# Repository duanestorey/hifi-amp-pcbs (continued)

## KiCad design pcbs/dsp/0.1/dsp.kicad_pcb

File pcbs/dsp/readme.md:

## Digital Signal Processing (DSP)

This PCB allows switching of 4 analog stereo inputs and one 5.1 channel input into 5.1.  Channels that are missing
can be created.  It is based on the AX2358 IC.

### Version History

- 1.0: Initial Release
- 1.2: Did an initial build.  Seems like there is digital noise on the output, likely from the I2C signals sharing the audio ground.  This design now has a digital and analog ground on the board - it'll use the digital ground for the AX2358 IC, but use the analog ground for the channel outputs.

### Speciality Components

* AX2358 Channel switching IC
* Nichicon Muse ES 25V 10uF

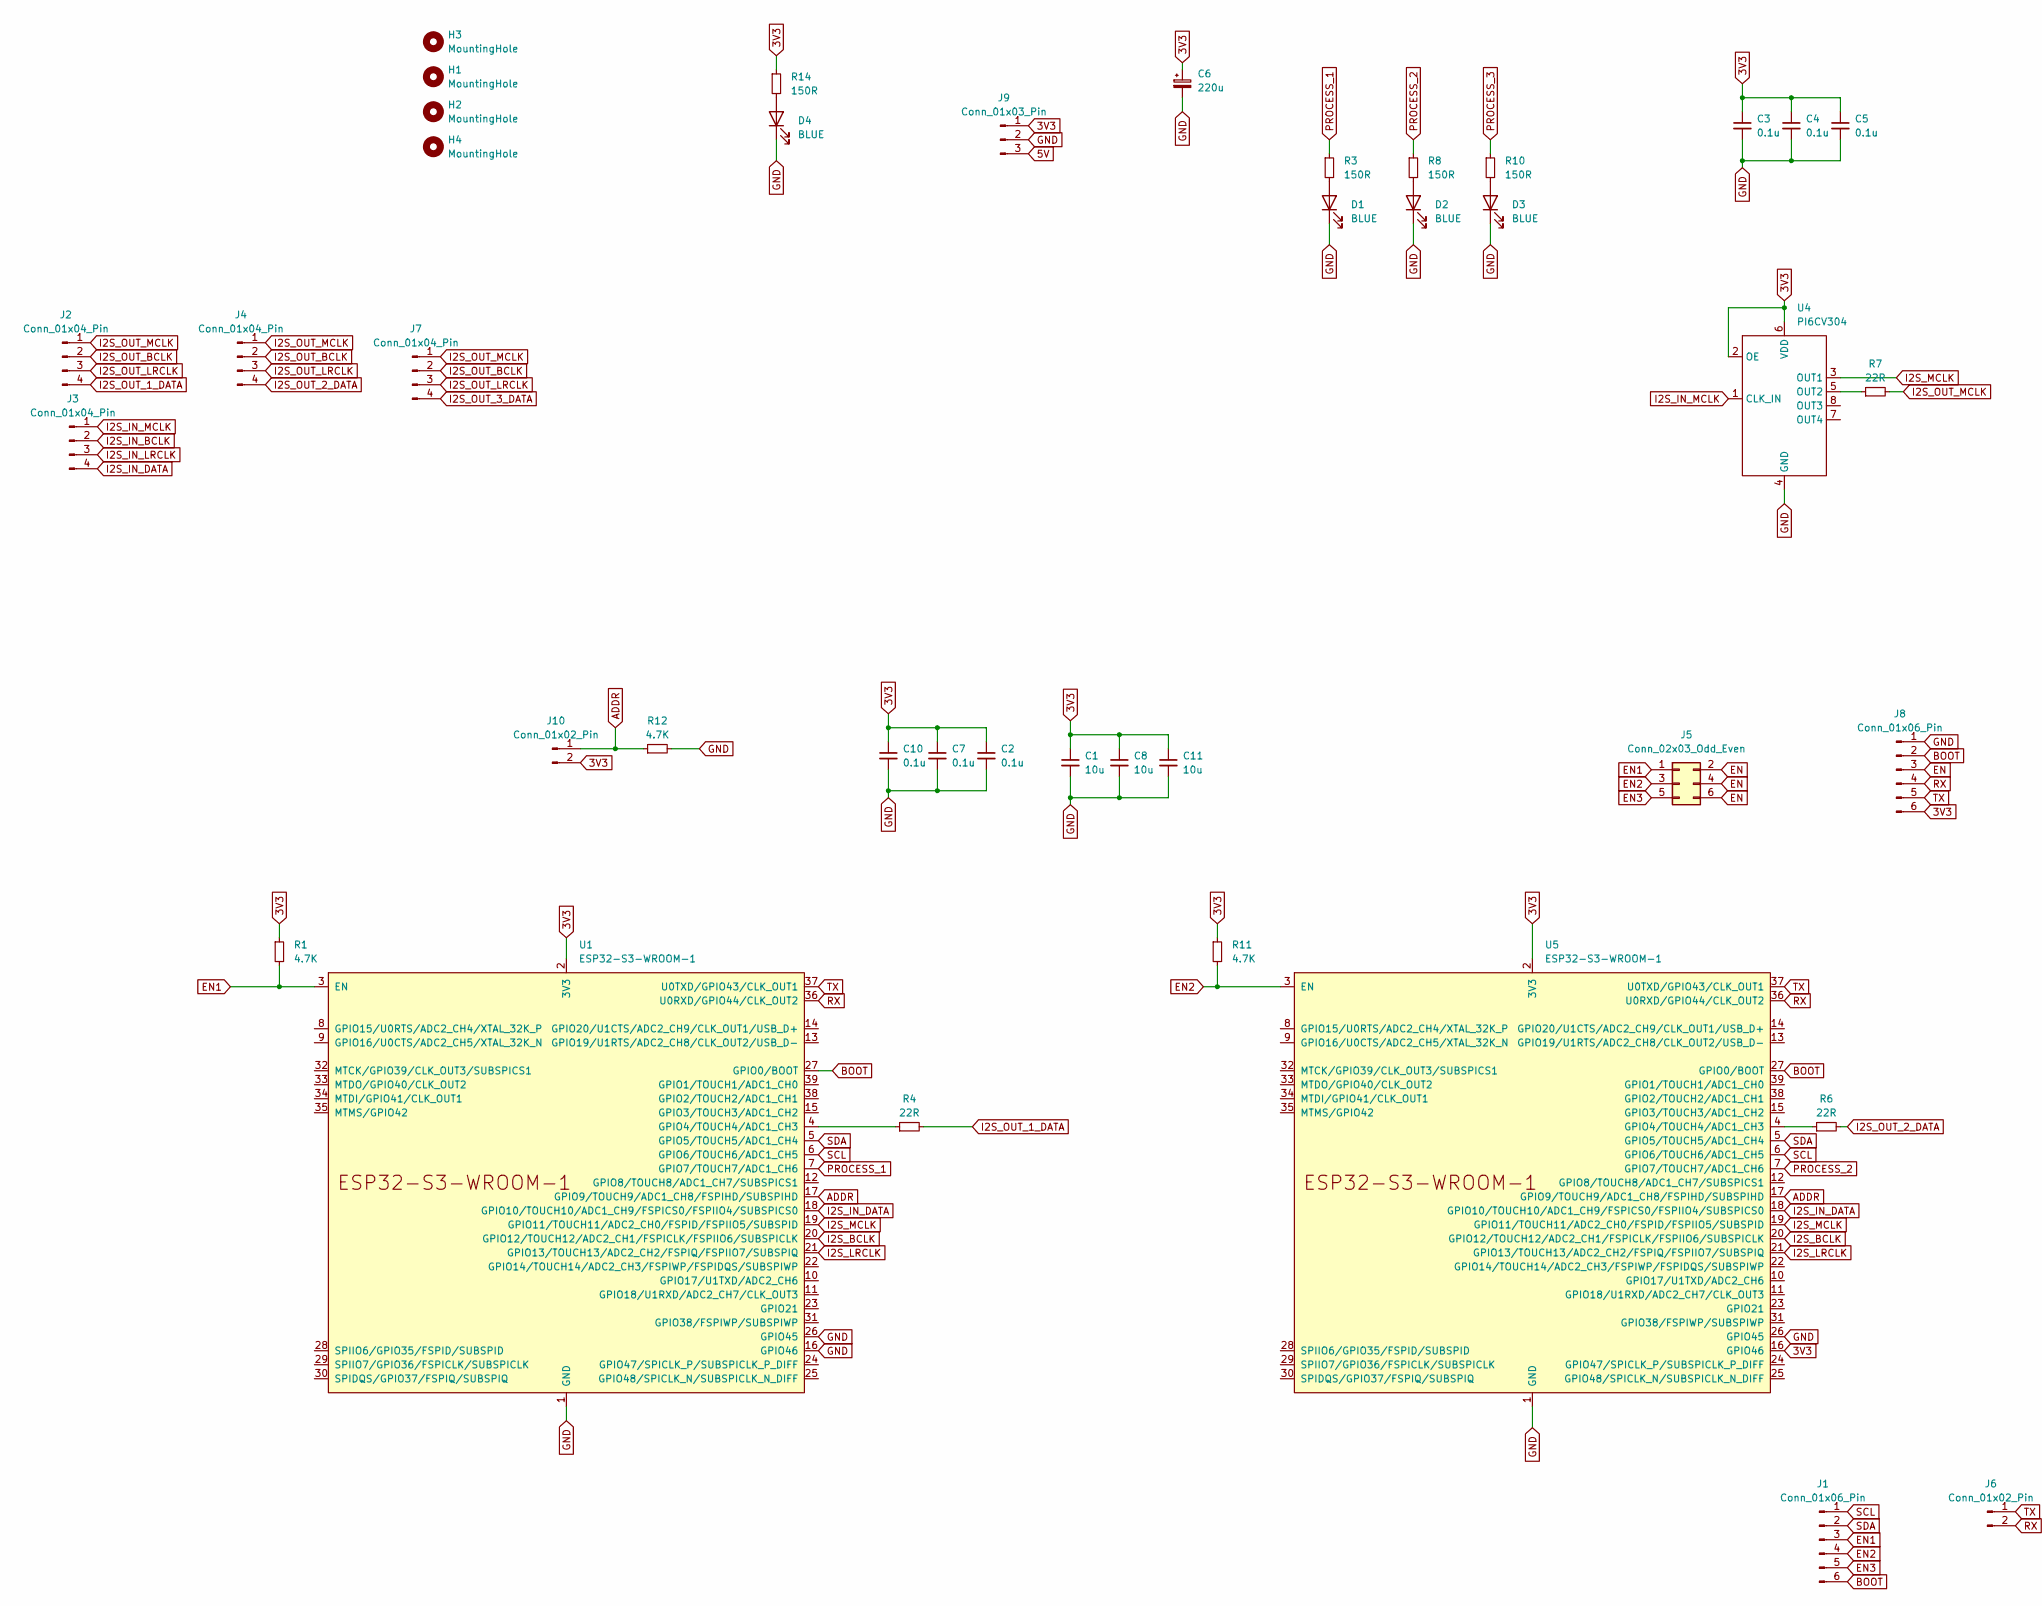
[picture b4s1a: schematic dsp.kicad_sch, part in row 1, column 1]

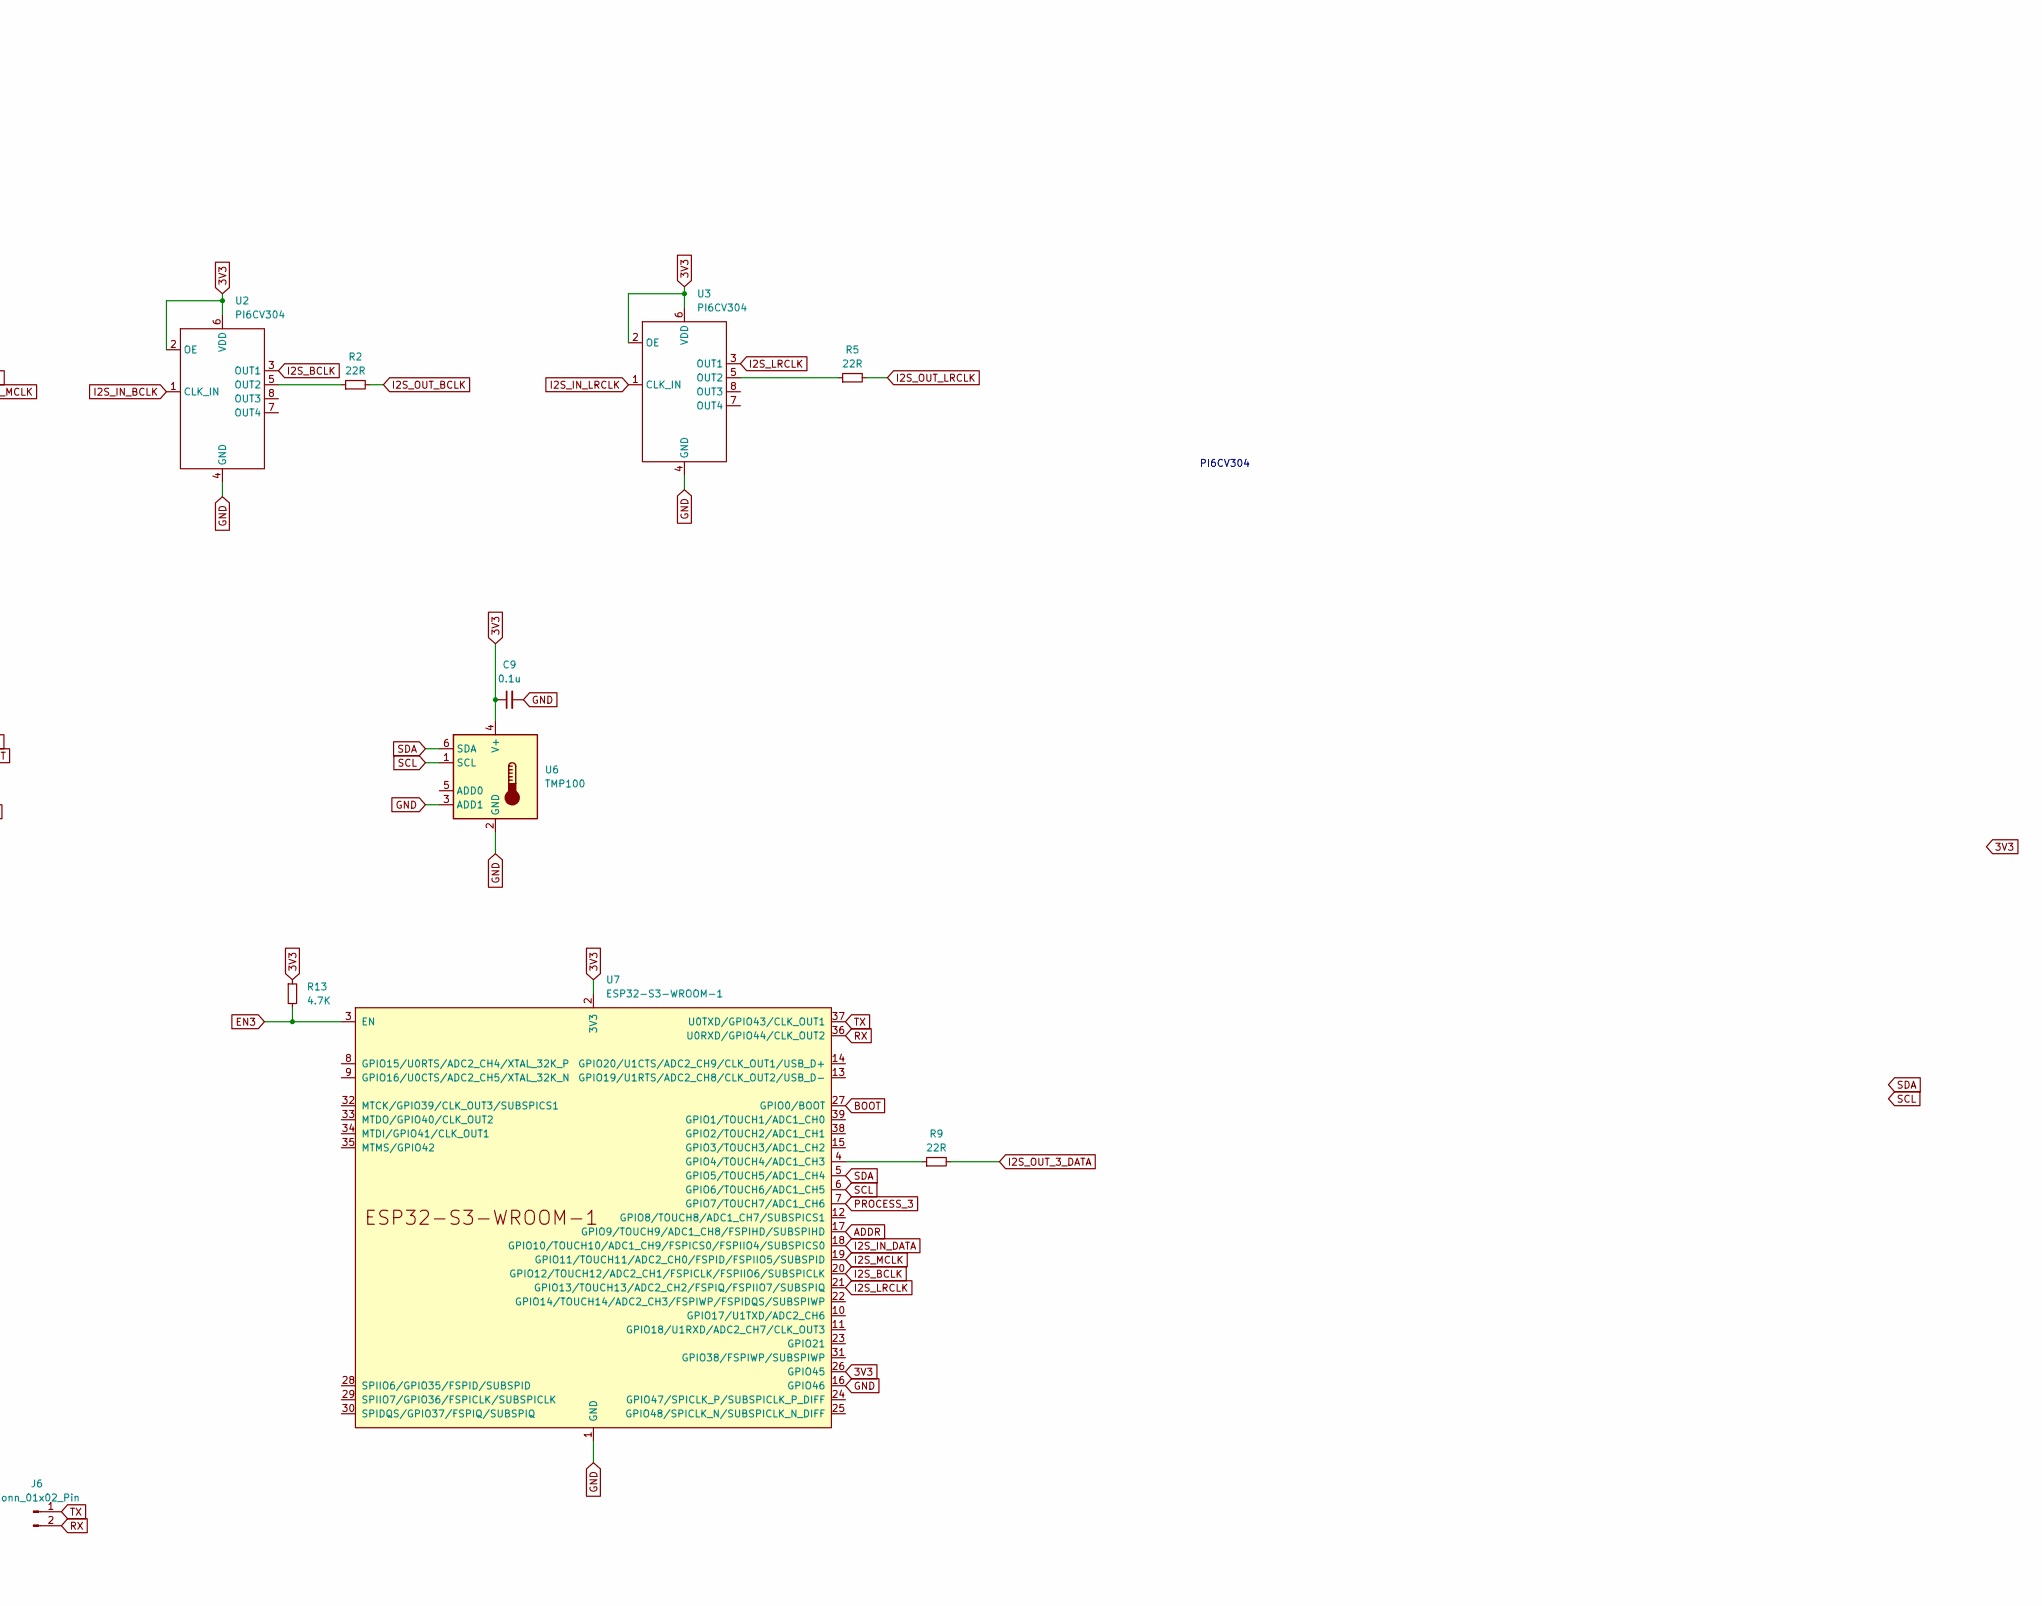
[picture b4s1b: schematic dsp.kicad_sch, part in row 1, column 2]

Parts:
C1, C8, C11: 10u; C_0805_2012Metric_Pad1.18x1.45mm_HandSolder
C2, C3, C4, C5, C7, C9, C10: 0.1u; C_0603_1608Metric_Pad1.08x0.95mm_HandSolder
C6: 220u; CP_Radial_D6.3mm_P2.50mm; LCSC C4747974
D1, D2, D3, D4: BLUE; D_0603_1608Metric; LCSC C84259
H1, H2, H3, H4: MountingHole; MountingHole_3.2mm_M3_DIN965_Pad_TopOnly
J1: Conn_01x06_Pin; JST_PH_B6B-PH-K_1x06_P2.00mm_Vertical
J2, J3, J4, J7: Conn_01x04_Pin; JST_PH_B4B-PH-K_1x04_P2.00mm_Vertical
J5: Conn_02x03_Odd_Even; PinHeader_2x03_P2.54mm_Vertical
J6: Conn_01x02_Pin; JST_PH_B2B-PH-K_1x02_P2.00mm_Vertical
J8: Conn_01x06_Pin; PinHeader_1x06_P2.54mm_Vertical
J9: Conn_01x03_Pin; JST_PH_B3B-PH-K_1x03_P2.00mm_Vertical
J10: Conn_01x02_Pin; PinHeader_1x02_P2.54mm_Vertical
R1, R11, R12, R13: 4.7K; R_0603_1608Metric; LCSC C23162
R2, R4, R5, R6, R7, R9: 22R; R_0603_1608Metric
R3, R8, R10, R14: 150R; R_0603_1608Metric; LCSC C22808
U1, U5, U7: ESP32-S3-WROOM-1; Mouser 356-ESP32S3WRM1N16R8
U2, U3, U4: PI6CV304; TSSOP-8_4.4x3mm_P0.65mm
U6: TMP100; SOT-23-6

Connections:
3V3: C1.1, C2.1, C3.1, C4.1, C5.1, C6.1, C7.1, C8.1, C9.1, C10.1, C11.1, J8.6, J9.1, J10.2, R1.1, R11.1, R13.1, R14.1, U1.2 (3V3), U2.2 (OE), U2.6 (VDD), U3.2 (OE), U3.6 (VDD), U4.2 (OE), U4.6 (VDD), U5.2 (3V3), U5.16 (GPIO46), U6.4 (V+), U7.2 (3V3), U7.26 (GPIO45)
5V: J9.3
ADDR: J10.1, R12.1, U1.17 (GPIO9/TOUCH9/ADC1_CH8/FSPIHD/SUBSPIHD), U5.17 (GPIO9/TOUCH9/ADC1_CH8/FSPIHD/SUBSPIHD), U7.17 (GPIO9/TOUCH9/ADC1_CH8/FSPIHD/SUBSPIHD)
BOOT: J1.6, J8.2, U1.27 (GPIO0/BOOT), U5.27 (GPIO0/BOOT), U7.27 (GPIO0/BOOT)
EN: J5.2, J5.4, J5.6, J8.3
EN1: J1.3, J5.1, R1.2, U1.3 (EN)
EN2: J1.4, J5.3, R11.2, U5.3 (EN)
EN3: J1.5, J5.5, R13.2, U7.3 (EN)
GND: C1.2, C2.2, C3.2, C4.2, C5.2, C6.2, C7.2, C8.2, C9.2, C10.2, C11.2, D1.1 (K), D2.1 (K), D3.1 (K), D4.1 (K), J8.1, J9.2, R12.2, U1.1 (GND), U1.16 (GPIO46), U1.26 (GPIO45), U1.40 (GND), U1.41 (GND), U2.4 (GND), U3.4 (GND), U4.4 (GND), U5.1 (GND), U5.26 (GPIO45), U5.40 (GND), U5.41 (GND), U6.2 (GND), U6.3 (ADD1), U7.1 (GND), U7.16 (GPIO46), U7.40 (GND), U7.41 (GND)
I2S_BCLK: U1.20 (GPIO12/TOUCH12/ADC2_CH1/FSPICLK/FSPIIO6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), U2.3 (OUT1), U5.20 (GPIO12/TOUCH12/ADC2_CH1/FSPICLK/FSPIIO6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), U7.20 (GPIO12/TOUCH12/ADC2_CH1/FSPICLK/FSPIIO6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)
I2S_IN_BCLK: J3.2, U2.1 (CLK_IN)
I2S_IN_DATA: J3.4, U1.18 (GPIO10/TOUCH10/ADC1_CH9/FSPICS0/FSPIIO4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), U5.18 (GPIO10/TOUCH10/ADC1_CH9/FSPICS0/FSPIIO4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), U7.18 (GPIO10/TOUCH10/ADC1_CH9/FSPICS0/FSPIIO4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)
I2S_IN_LRCLK: J3.3, U3.1 (CLK_IN)
I2S_IN_MCLK: J3.1, U4.1 (CLK_IN)
I2S_LRCLK: U1.21 (GPIO13/TOUCH13/ADC2_CH2/FSPIQ/FSPIIO7/S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), U3.3 (OUT1), U5.21 (GPIO13/TOUCH13/ADC2_CH2/FSPIQ/FSPIIO7/S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), U7.21 (GPIO13/TOUCH13/ADC2_CH2/FSPIQ/FSPIIO7/S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)
I2S_MCLK: U1.19 (GPIO11/TOUCH11/ADC2_CH0/FSPID/FSPIIO5/S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), U4.3 (OUT1), U5.19 (GPIO11/TOUCH11/ADC2_CH0/FSPID/FSPIIO5/S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), U7.19 (GPIO11/TOUCH11/ADC2_CH0/FSPID/FSPIIO5/S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)
I2S_OUT_1_DATA: J2.4, R4.2
I2S_OUT_2_DATA: J4.4, R6.2
I2S_OUT_3_DATA: J7.4, R9.2
I2S_OUT_BCLK: J2.2, J4.2, J7.2, R2.2
I2S_OUT_LRCLK: J2.3, J4.3, J7.3, R5.2
I2S_OUT_MCLK: J2.1, J4.1, J7.1, R7.2
unnamed: D1.2 (A), R3.2
unnamed: D2.2 (A), R8.2
unnamed: D3.2 (A), R10.2
unnamed: D4.2 (A), R14.2
unnamed: R4.1, U1.4 (GPIO4/TOUCH4/ADC1_CH3)
unnamed: R2.1, U2.5 (OUT2)
unnamed: R5.1, U3.5 (OUT2)
unnamed: R7.1, U4.5 (OUT2)
unnamed: R6.1, U5.4 (GPIO4/TOUCH4/ADC1_CH3)
unnamed: R9.1, U7.4 (GPIO4/TOUCH4/ADC1_CH3)
PROCESS_1: R3.1, U1.7 (GPIO7/TOUCH7/ADC1_CH6)
PROCESS_2: R8.1, U5.7 (GPIO7/TOUCH7/ADC1_CH6)
PROCESS_3: R10.1, U7.7 (GPIO7/TOUCH7/ADC1_CH6)
RX: J6.2, J8.4, U1.36 (U0RXD/GPIO44/CLK_OUT2), U5.36 (U0RXD/GPIO44/CLK_OUT2), U7.36 (U0RXD/GPIO44/CLK_OUT2)
SCL: J1.1, U1.6 (GPIO6/TOUCH6/ADC1_CH5), U5.6 (GPIO6/TOUCH6/ADC1_CH5), U6.1 (SCL), U7.6 (GPIO6/TOUCH6/ADC1_CH5)
SDA: J1.2, U1.5 (GPIO5/TOUCH5/ADC1_CH4), U5.5 (GPIO5/TOUCH5/ADC1_CH4), U6.6 (SDA), U7.5 (GPIO5/TOUCH5/ADC1_CH4)
TX: J6.1, J8.5, U1.37 (U0TXD/GPIO43/CLK_OUT1), U5.37 (U0TXD/GPIO43/CLK_OUT1), U7.37 (U0TXD/GPIO43/CLK_OUT1)

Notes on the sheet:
PI6CV304

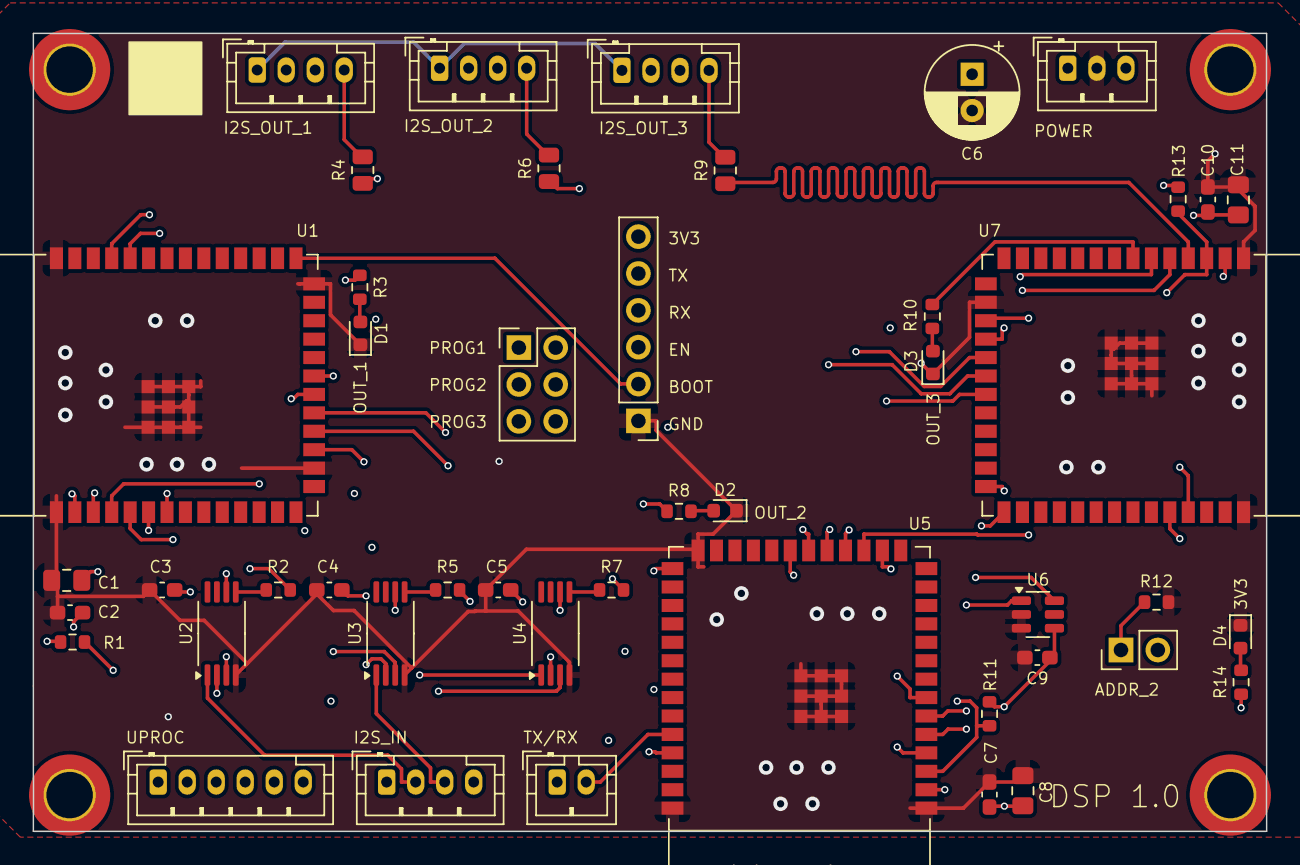
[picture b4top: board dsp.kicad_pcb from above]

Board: 4 copper layers, 85.0 x 55.0 mm, 50 parts (0 on the bottom side), 38 nets.

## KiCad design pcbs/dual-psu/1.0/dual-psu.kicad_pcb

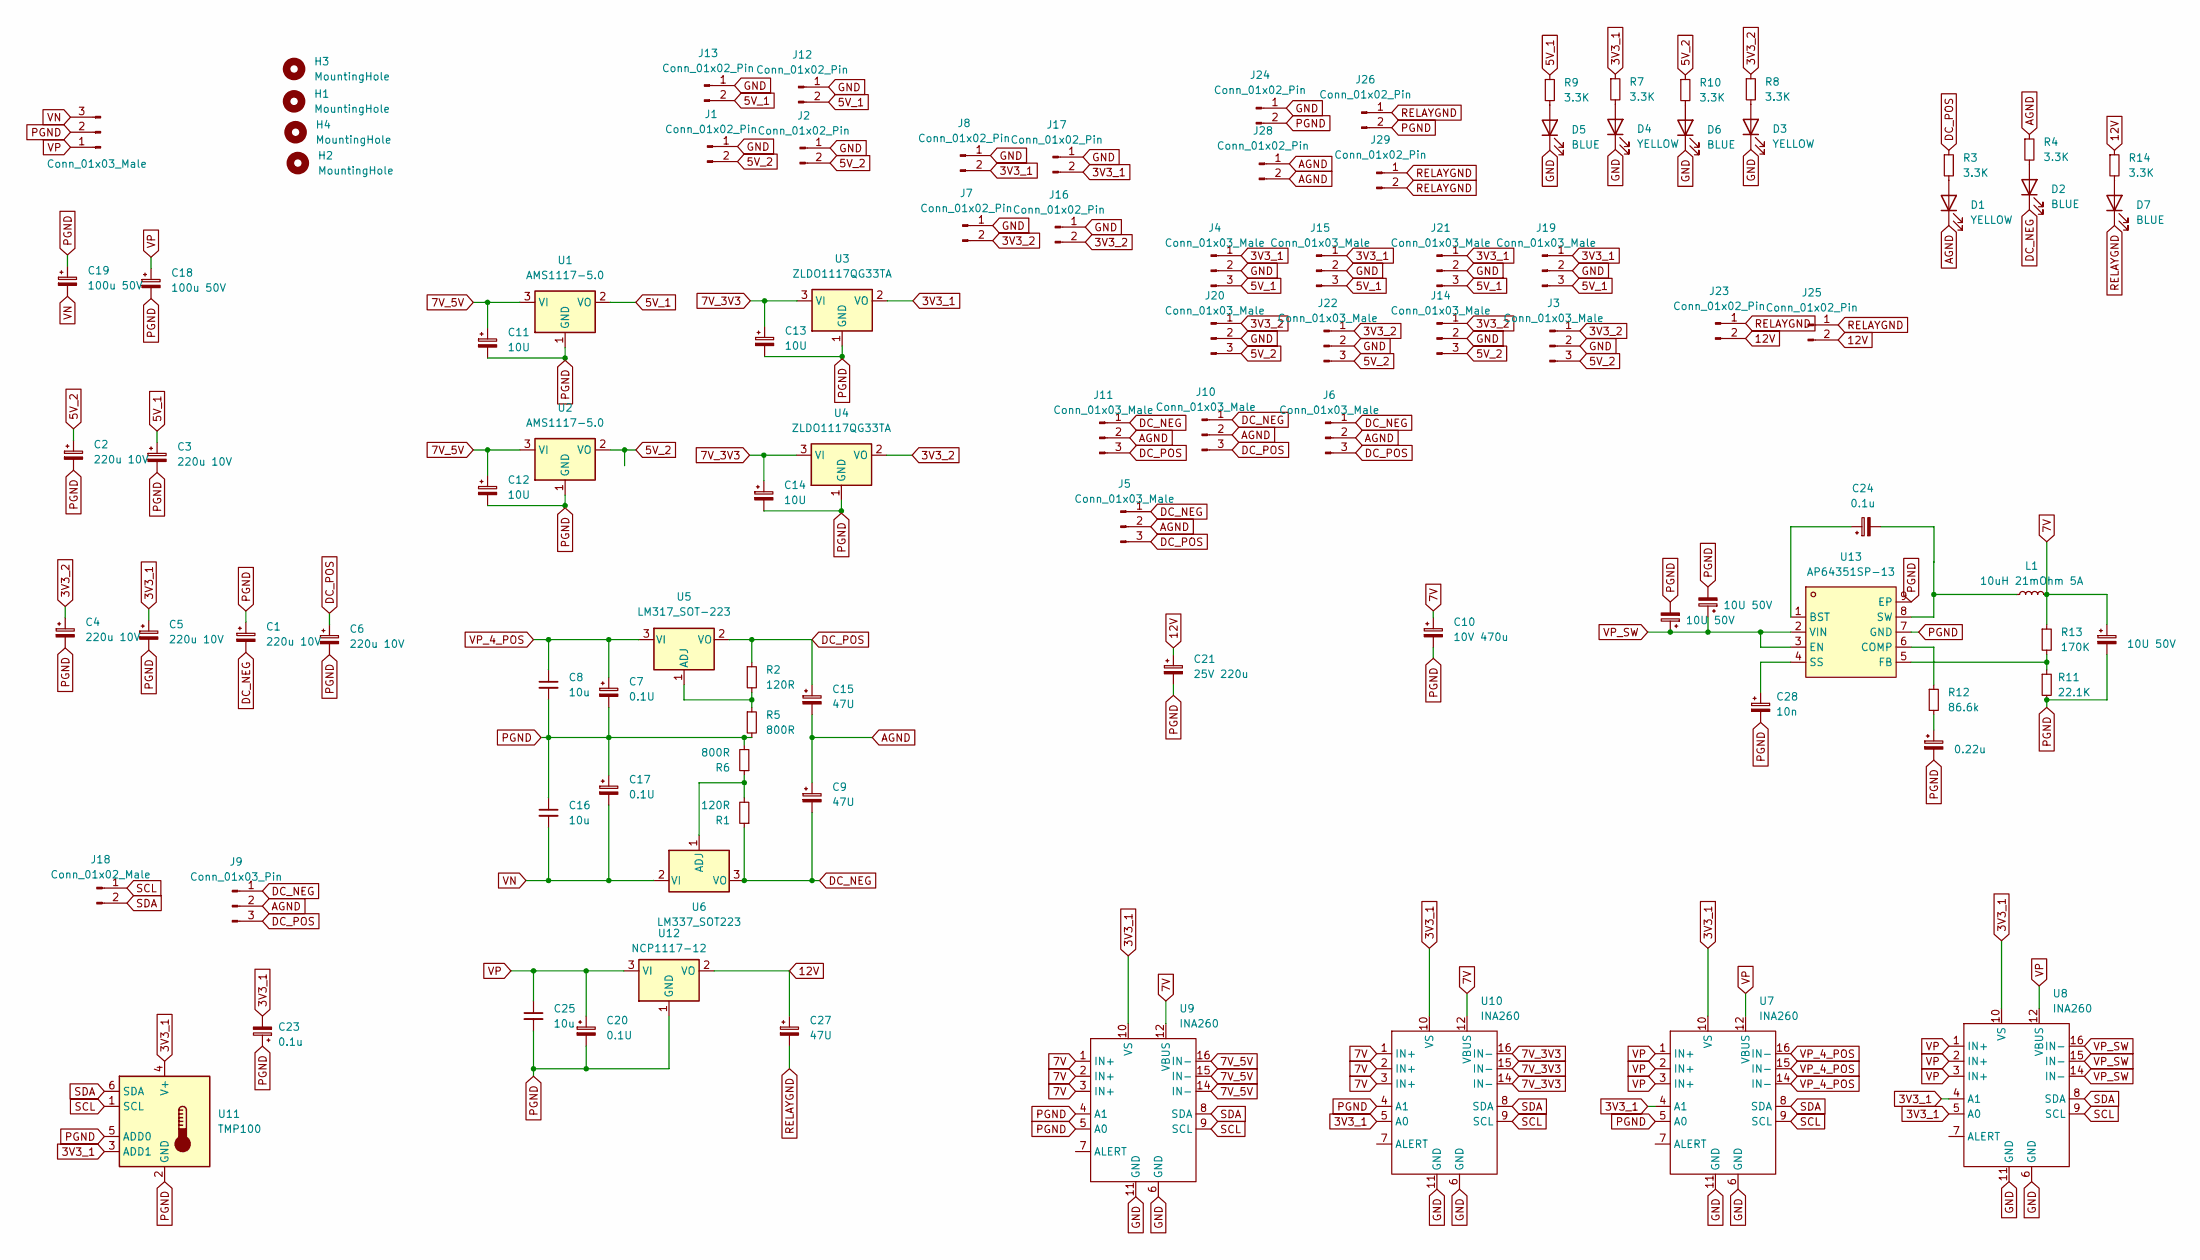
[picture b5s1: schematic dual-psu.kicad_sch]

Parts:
C1, C2, C3, C4, C5, C6: 220u 10V; CP_Radial_D6.3mm_P2.50mm
C7, C17, C20: 0.1U; C_0603_1608Metric_Pad1.08x0.95mm_HandSolder
C8, C16, C25: 10u; C_1206_3216Metric_Pad1.33x1.80mm_HandSolder
C9, C15, C27: 47U; C_1206_3216Metric_Pad1.33x1.80mm_HandSolder
C10: 10V 470u; CP_Radial_D8.0mm_P3.50mm
C11, C12, C13, C14: 10U; C_1206_3216Metric_Pad1.33x1.80mm_HandSolder
C18, C19: 100u 50V; CP_Radial_D8.0mm_P3.50mm
C21: 25V 220u; CP_Radial_D8.0mm_P3.50mm
C22, C29, C30: 10U 50V; C_1206_3216Metric_Pad1.33x1.80mm_HandSolder
C23, C24: 0.1u; C_0805_2012Metric_Pad1.18x1.45mm_HandSolder
C26: 0.22u; C_0805_2012Metric_Pad1.18x1.45mm_HandSolder
C28: 10n; C_0805_2012Metric_Pad1.18x1.45mm_HandSolder
D1: YELLOW; LED_0603_1608Metric
D2, D7: BLUE; LED_0603_1608Metric
D3, D4: YELLOW; LED_0805_2012Metric_Pad1.15x1.40mm_HandSolder
D5, D6: BLUE; LED_0805_2012Metric_Pad1.15x1.40mm_HandSolder
H1, H2, H3, H4: MountingHole; MountingHole_3.2mm_M3_DIN965_Pad_TopOnly
J1, J2, J7, J8, J12, J13, J16, J17, J23, J25, J28, J29: Conn_01x02_Pin; JST_PH_B2B-PH-K_1x02_P2.00mm_Vertical
J3, J4, J5, J6, J10, J11, J14, J15, J19, J20, J21, J22: Conn_01x03_Male; JST_PH_B3B-PH-K_1x03_P2.00mm_Vertical
J9: Conn_01x03_Pin; PinHeader_1x03_P2.54mm_Vertical
J18: Conn_01x02_Male; JST_PH_B2B-PH-K_1x02_P2.00mm_Vertical
J24, J26: Conn_01x02_Pin; PinHeader_1x02_P2.54mm_Vertical
J27: Conn_01x03_Male; JST_VH_B3P-VH_1x03_P3.96mm_Vertical
L1: 10uH 21mOhm 5A; L_Vishay_IHLP-4040; Mouser 704-DR1040-7R0-R
R1, R2: 120R; R_0603_1608Metric_Pad0.98x0.95mm_HandSolder
R3, R4, R7, R8, R9, R10, R14: 3.3K; R_0603_1608Metric_Pad0.98x0.95mm_HandSolder
R5, R6: 800R; R_0603_1608Metric_Pad0.98x0.95mm_HandSolder
R11: 22.1K; R_0603_1608Metric_Pad0.98x0.95mm_HandSolder; Mouser 603-RC0603JR-07820KP
R12: 86.6k; R_0603_1608Metric_Pad0.98x0.95mm_HandSolder; Mouser 71-CRCW0603-86.6K-E3
R13: 170K; R_0603_1608Metric_Pad0.98x0.95mm_HandSolder
U1, U2: AMS1117-5.0; SOT-223-3_TabPin2; Mouser 926-LM1117MPX5.0NOPB
U3, U4: ZLDO1117QG33TA; SOT-223-3_TabPin2; Mouser ZLDO1117QG33TA
U5: LM317_SOT-223; SOT-223-3_TabPin2; Mouser 595-LM317DCY
U6: LM337_SOT223; SOT-223-3_TabPin2; Mouser 926-LM337IMPX/NOPB
U7, U8, U9, U10: INA260; TSSOP-16_4.4x5mm_P0.65mm
U11: TMP100; SOT-23-6; Mouser 595-TMP100NA/3K
U12: NCP1117-12; SOT-223; Mouser 863-NCP1117ST12T3G
U13: AP64351SP-13; SOIC-8_L4.9-W3.9-P1.27-LS6.0-BL-EP; LCSC Part C3192339

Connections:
3V3_1: C5.1, C23.2, J4.1, J8.2, J15.1, J17.2, J19.1, J21.1, R7.1, U3.2 (VO), U7.4 (A1), U7.10 (VS), U8.4 (A1), U8.5 (A0), U8.10 (VS), U9.10 (VS), U10.5 (A0), U10.10 (VS), U11.3 (ADD1), U11.4 (V+)
3V3_2: C4.1, J3.1, J7.2, J14.1, J16.2, J20.1, J22.1, R8.1, U4.2 (VO)
5V_1: C3.1, J4.3, J12.2, J13.2, J15.3, J19.3, J21.3, R9.1, U1.2 (VO)
5V_2: C2.1, J1.2, J2.2, J3.3, J14.3, J20.3, J22.3, R10.1, U2.2 (VO)
7V: C10.1, C22.1, L1.2, R13.1, U9.1 (IN+), U9.2 (IN+), U9.3 (IN+), U9.12 (VBUS), U10.1 (IN+), U10.2 (IN+), U10.3 (IN+), U10.12 (VBUS)
7V_3V3: C13.1, C14.1, U3.3 (VI), U4.3 (VI), U10.14 (IN-), U10.15 (IN-), U10.16 (IN-)
7V_5V: C11.1, C12.1, U1.3 (VI), U2.3 (VI), U9.14 (IN-), U9.15 (IN-), U9.16 (IN-)
12V: C21.1, C27.1, J23.2, J25.2, R14.1, U12.2 (VO)
AGND: C9.1, C15.2, D1.1 (K), J5.2, J6.2, J9.2, J10.2, J11.2, J28.1, J28.2, R4.1
DC_NEG: C1.2, C9.2, D2.1 (K), J5.1, J6.1, J9.1, J10.1, J11.1, R1.1, U6.3 (VO)
DC_POS: C6.1, C15.1, J5.3, J6.3, J9.3, J10.3, J11.3, R2.1, R3.1, U5.2 (VO)
GND: D3.1 (K), D4.1 (K), D5.1 (K), D6.1 (K), J1.1, J2.1, J3.2, J4.2, J7.1, J8.1, J12.1, J13.1, J14.2, J15.2, J16.1, J17.1, J19.2, J20.2, J21.2, J22.2, J24.1, U7.6 (GND), U7.11 (GND), U8.6 (GND), U8.11 (GND), U9.6 (GND), U9.11 (GND), U10.6 (GND), U10.11 (GND)
unnamed: C26.1, R12.2
unnamed: D1.2 (A), R3.2
unnamed: D2.2 (A), R4.2
unnamed: D3.2 (A), R8.2
unnamed: D4.2 (A), R7.2
unnamed: D5.2 (A), R9.2
unnamed: D6.2 (A), R10.2
unnamed: D7.2 (A), R14.2
unnamed: R2.2, R5.1, U5.1 (ADJ)
unnamed: R1.2, R6.1, U6.1 (ADJ)
unnamed: C24.1, U13.1 (BST)
unnamed: R12.1, U13.6 (COMP)
unnamed: R11.1, R13.2, U13.5 (FB)
unnamed: C28.1, U13.4 (SS)
unnamed: C24.2, L1.1, U13.8 (SW)
PGND: C1.1, C2.2, C3.2, C4.2, C5.2, C6.2, C7.2, C8.2, C10.2, C11.2, C12.2, C13.2, C14.2, C16.1, C17.1, C18.2, C19.1, C20.2, C21.2, C22.2, C23.1, C25.2, C26.2, C28.2, C29.2, C30.2, J24.2, J26.2, J27.2, R5.2, R6.2, R11.2, U1.1 (GND), U2.1 (GND), U3.1 (GND), U4.1 (GND), U7.5 (A0), U9.4 (A1), U9.5 (A0), U10.4 (A1), U11.2 (GND), U11.5 (ADD0), U12.1 (GND), U13.7 (GND), U13.9 (EP)
RELAYGND: C27.2, D7.1 (K), J23.1, J25.1, J26.1, J29.1, J29.2
SCL: J18.1, U7.9 (SCL), U8.9 (SCL), U9.9 (SCL), U10.9 (SCL), U11.1 (SCL)
SDA: J18.2, U7.8 (SDA), U8.8 (SDA), U9.8 (SDA), U10.8 (SDA), U11.6 (SDA)
VN: C16.2, C17.2, C19.2, J27.3, U6.2 (VI)
VP: C18.1, C20.1, C25.1, J27.1, U7.1 (IN+), U7.2 (IN+), U7.3 (IN+), U7.12 (VBUS), U8.1 (IN+), U8.2 (IN+), U8.3 (IN+), U8.12 (VBUS), U12.3 (VI)
VP_4_POS: C7.1, C8.1, U5.3 (VI), U7.14 (IN-), U7.15 (IN-), U7.16 (IN-)
VP_SW: C29.1, C30.1, U8.14 (IN-), U8.15 (IN-), U8.16 (IN-), U13.2 (VIN), U13.3 (EN)

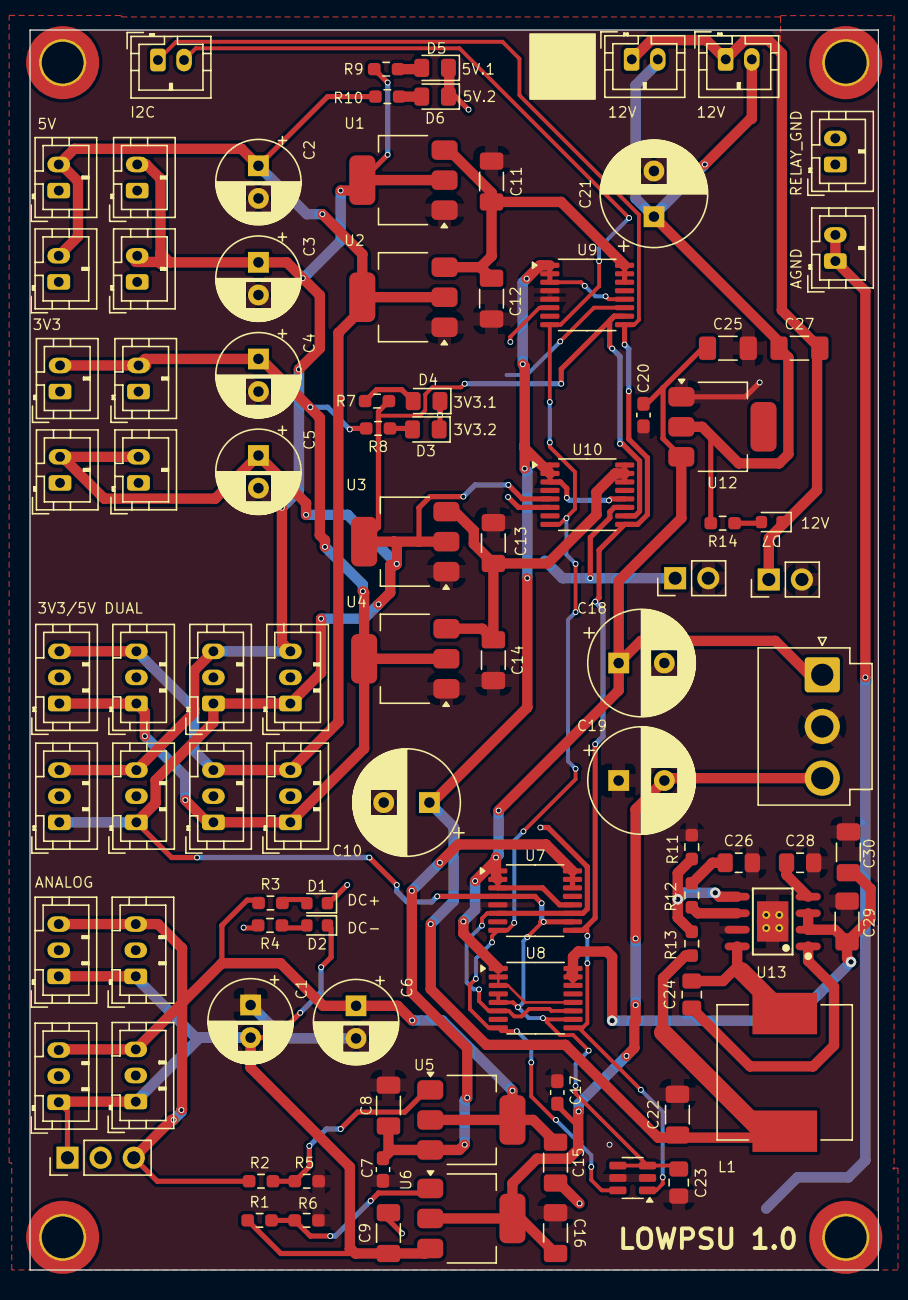
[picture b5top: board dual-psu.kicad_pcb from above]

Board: 2 copper layers, 65.0 x 95.0 mm, 98 parts (0 on the bottom side), 35 nets.

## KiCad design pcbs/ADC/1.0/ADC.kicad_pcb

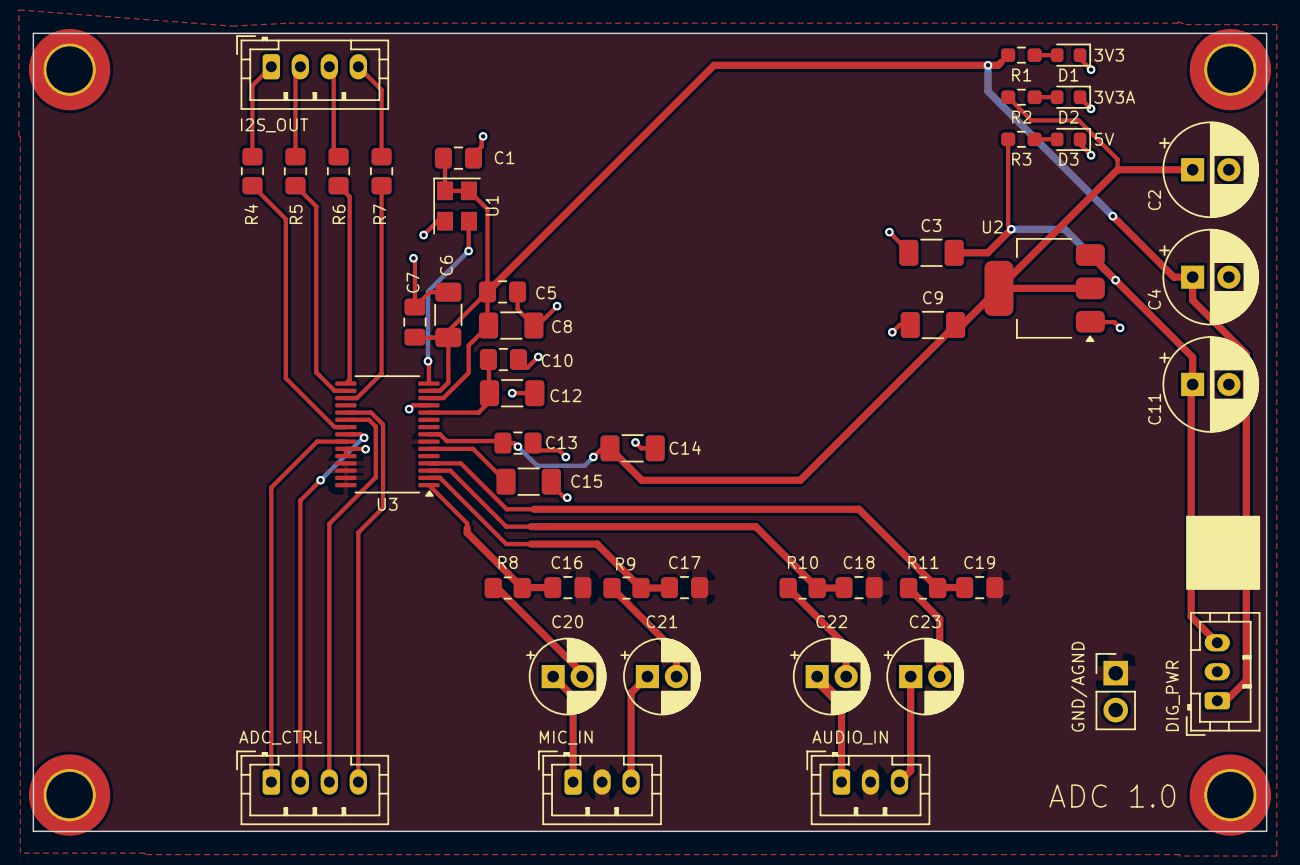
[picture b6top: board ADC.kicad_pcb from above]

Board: 2 copper layers, 85.0 x 55.0 mm, 50 parts (0 on the bottom side), 35 nets.

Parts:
C1, C5, C7, C10, C13: 0.1u; C_0805_2012Metric_Pad1.18x1.45mm_HandSolder
C2, C4, C11: 470u; CP_Radial_D6.3mm_P2.50mm
C3, C6, C8, C9, C12, C14: 10u; C_1206_3216Metric_Pad1.33x1.80mm_HandSolder
C15: 1u; C_1206_3216Metric_Pad1.33x1.80mm_HandSolder
C16, C17, C18, C19: 10n C0G; C_0805_2012Metric_Pad1.18x1.45mm_HandSolder
C20, C21, C22, C23: 10u NICHICON 25V; CP_Radial_D5.0mm_P2.00mm
D1, D3: BLUE; LED_0603_1608Metric
D2: YELLOW; LED_0603_1608Metric
H1, H2, H3, H4: MountingHole; MountingHole_3.2mm_M3_DIN965_Pad_TopOnly
J1, J4: Conn_01x04_Pin; JST_PH_B4B-PH-K_1x04_P2.00mm_Vertical
J2: Conn_01x02_Male; PinHeader_1x02_P2.54mm_Vertical
J3, J5, J6: Conn_01x03_Pin; JST_PH_B3B-PH-K_1x03_P2.00mm_Vertical
R1: 150R; R_0603_1608Metric_Pad0.98x0.95mm_HandSolder
R2: 650R; R_0603_1608Metric_Pad0.98x0.95mm_HandSolder
R3: 1.3K; R_0603_1608Metric_Pad0.98x0.95mm_HandSolder
R4, R5, R6, R7: 22R; R_0805_2012Metric_Pad1.20x1.40mm_HandSolder
R8, R9, R10, R11: 100R; R_0805_2012Metric_Pad1.20x1.40mm_HandSolder
U1: ASDMB-xxxMHz; Oscillator_SMD_Abracon_ASE-4Pin_3.2x2.5mm
U2: ZLDO1117QG33TA; SOT-223-3_TabPin2
U3: PCM1863; TSSOP-30_4.4x7.8mm_P0.5mm

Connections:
3V3: C1.1, C4.1, C5.1, C6.1, C7.1, C8.1, J3.1, R1.2, U1.1 (Standby), U1.4 (VDD), U3.13 (DVDD), U3.14 (IOVDD)
3V3A: C2.1, C9.2, C13.1, C14.1, R2.2, U2.2 (VO), U3.8 (AVDD)
5V: C3.2, C11.1, J3.3, R3.2, U2.3 (VI)
ADC_GPIO1: J4.3, U3.21 (GPIO1/INTA/DMI)
ADC_INT: J4.4, U3.20 (GPIO2/INTB/DMCLK)
AGND: C16.1, C17.2, C18.1, C19.2, J2.1, J5.2, J6.2, U3.7 (AGND), U3.27 (VINL4), U3.28 (VINR4), U3.29 (VINL3), U3.30 (VINR3)
GND: C1.2, C3.1, C4.2, C5.2, C6.2, C7.2, C8.2, C9.1, C10.2, C11.2, C12.2, C13.2, C14.2, C15.2, D1.1 (K), D2.1 (K), D3.1 (K), J2.2, J3.2, U1.2 (GND), U2.1 (GND), U3.12 (DGND), U3.25 (MS/AD), U3.26 (MD0)
I2S_BCLK_OUT: J1.2, R5.2
I2S_DATA_OUT: J1.4, R7.2
I2S_LRCLK_OUT: J1.3, R6.2
I2S_MCLK_OUT: J1.1, R4.2
LDO: C10.1, C12.1, U3.11 (LDO)
LEFT_IN: C22.1, J6.1
MIC_LEFT_IN: C20.1, J5.1
MIC_RIGHT_IN: C21.1, J5.3
unnamed: C20.2, R8.1
unnamed: C21.2, R9.1
unnamed: C22.2, R10.1
unnamed: C23.2, R11.1
unnamed: D1.2 (A), R1.1
unnamed: D2.2 (A), R2.1
unnamed: D3.2 (A), R3.1
unnamed: R5.1, U3.17 (BCLK)
unnamed: R7.1, U3.18 (DOUT)
unnamed: R6.1, U3.16 (LRCLK)
unnamed: R4.1, U3.22 (MOSI/GPIO0/DMIN2)
unnamed: C18.2, R10.2, U3.3 (VINL1)
unnamed: C16.2, R8.2, U3.1 (VINL2)
unnamed: C19.1, R11.2, U3.4 (VINR1)
unnamed: C17.1, R9.2, U3.2 (VINR2)
RIGHT_IN: C23.1, J6.3
SCL: J4.1, U3.24 (MC/SCL)
SCLKI: U1.3 (Out), U3.15 (SCLKI)
SDA: J4.2, U3.23 (MOSI/SDA)
VREF: C15.1, U3.6 (VREF)

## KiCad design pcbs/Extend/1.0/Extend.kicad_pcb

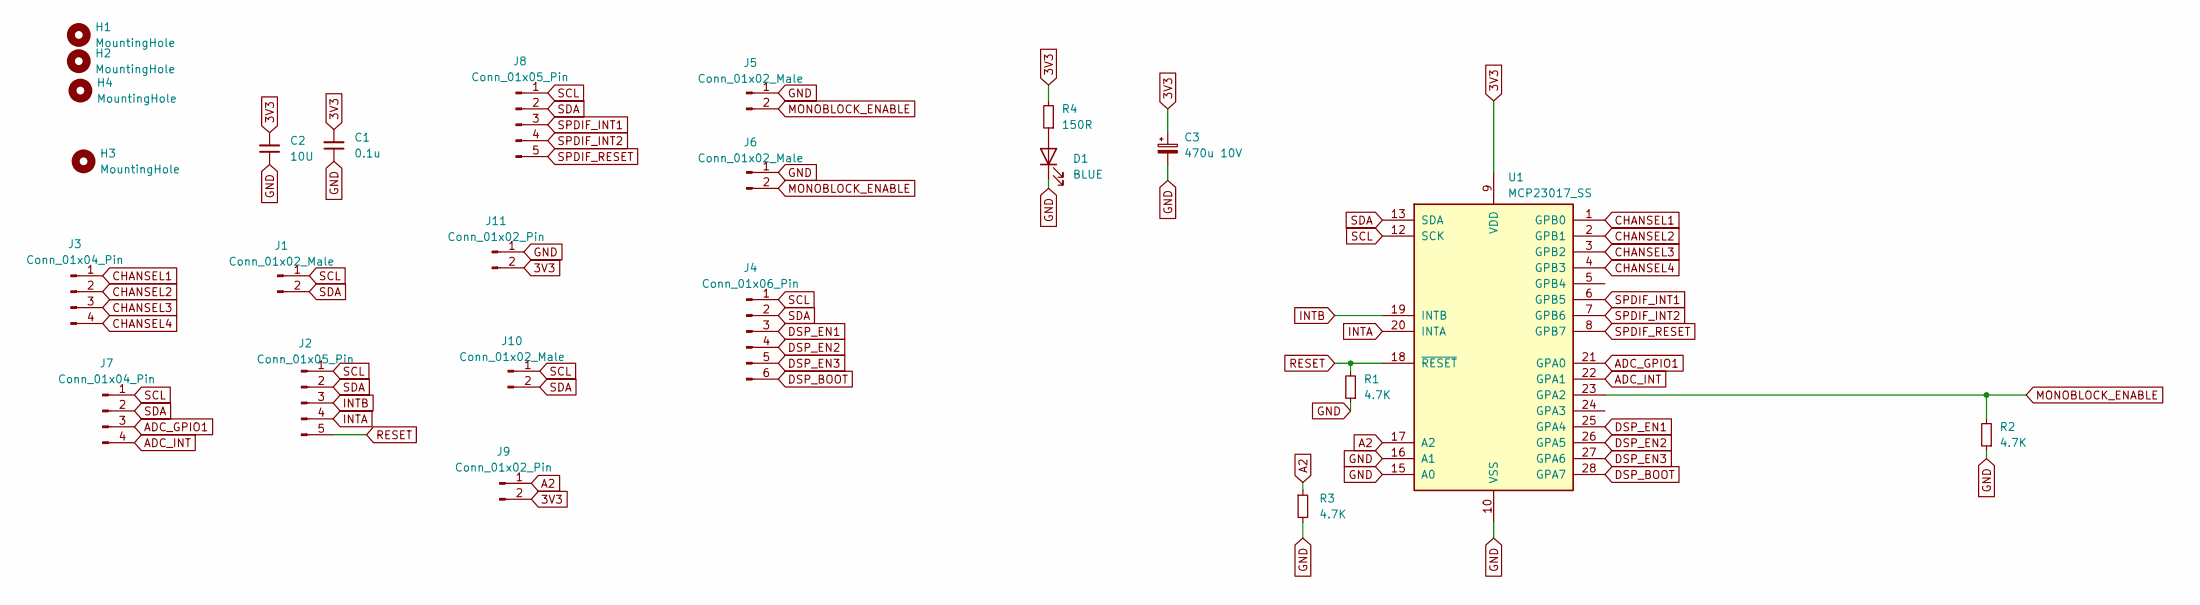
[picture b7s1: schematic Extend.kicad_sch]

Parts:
C1: 0.1u; C_0805_2012Metric_Pad1.18x1.45mm_HandSolder
C2: 10U; C_1206_3216Metric_Pad1.33x1.80mm_HandSolder
C3: 470u 10V; CP_Radial_D6.3mm_P2.50mm
D1: BLUE; LED_0603_1608Metric
H1, H2, H3, H4: MountingHole; MountingHole_3.2mm_M3_DIN965_Pad_TopOnly
J1, J5, J6, J10: Conn_01x02_Male; JST_PH_B2B-PH-K_1x02_P2.00mm_Vertical
J2, J8: Conn_01x05_Pin; JST_PH_B5B-PH-K_1x05_P2.00mm_Vertical
J3, J7: Conn_01x04_Pin; JST_PH_B4B-PH-K_1x04_P2.00mm_Vertical
J4: Conn_01x06_Pin; JST_PH_B6B-PH-K_1x06_P2.00mm_Vertical
J9: Conn_01x02_Pin; PinHeader_1x02_P2.54mm_Vertical
J11: Conn_01x02_Pin; JST_PH_B2B-PH-K_1x02_P2.00mm_Vertical
R1, R2, R3: 4.7K; R_0603_1608Metric_Pad0.98x0.95mm_HandSolder
R4: 150R; R_0603_1608Metric
U1: MCP23017_SS; SSOP-28_5.3x10.2mm_P0.65mm

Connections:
3V3: C1.2, C2.2, C3.1, J9.2, J11.2, R4.2, U1.9 (VDD)
A2: J9.1, R3.1, U1.17 (A2)
ADC_GPIO1: J7.3, U1.21 (GPA0)
ADC_INT: J7.4, U1.22 (GPA1)
CHANSEL1: J3.1, U1.1 (GPB0)
CHANSEL2: J3.2, U1.2 (GPB1)
CHANSEL3: J3.3, U1.3 (GPB2)
CHAN_EN: J3.4, U1.4 (GPB3)
DAC_XSMT: U1.24 (GPA3); also elsewhere on the board
DSP_BOOT: J4.6, U1.28 (GPA7)
DSP_EN1: J4.3, U1.25 (GPA4)
DSP_EN2: J4.4, U1.26 (GPA5)
DSP_EN3: J4.5, U1.27 (GPA6)
GND: C1.1, C2.1, C3.2, D1.1 (K), J5.1, J6.1, J11.1, R1.1, R2.1, R3.2, U1.10 (VSS), U1.15 (A0), U1.16 (A1)
INTA: J2.4, U1.20 (INTA)
INTB: J2.3, U1.19 (INTB)
MONOBLOCK_ENABLE: J5.2, J6.2, R2.2, U1.23 (GPA2)
unnamed: D1.2 (A), R4.1
RESET: J2.5, R1.2, U1.18 (~RESET)
SCL: J1.1, J2.1, J4.1, J7.1, J8.1, J10.1, U1.12 (SCK); also elsewhere on the board
SDA: J1.2, J2.2, J4.2, J7.2, J8.2, J10.2, U1.13 (SDA); also elsewhere on the board
SPDIF_INT1: J8.3, U1.6 (GPB5)
SPDIF_INT2: J8.4, U1.7 (GPB6)
SPDIF_RESET: J8.5, U1.8 (GPB7)
